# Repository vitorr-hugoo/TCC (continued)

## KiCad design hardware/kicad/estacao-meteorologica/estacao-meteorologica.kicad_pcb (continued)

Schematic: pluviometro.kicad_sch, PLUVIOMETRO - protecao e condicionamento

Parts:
C301, C302: 100 nF; C_0603_1608Metric; MPN CC0603KRX7R9BB104; LCSC C14663
D301: PESD5V0S1UL; D_SOD-882; MPN PESD5V0S1UL,315; LCSC C85402
D302: BAS70-04; SOT-23; MPN BAS70-04,215; LCSC C389351
J301: RJ11 6P6C, 90°; RJ11-TH_PCB-6P6C-90; MPN R-RJ11R06P-A800; LCSC C189750
R301: 10 kΩ; R_0603_1608Metric; MPN 0603WAF1002T5E; LCSC C25804
R302: 4.7 kΩ; R_0603_1608Metric; MPN 0603WAF4701T5E; LCSC C23162
R303: 1 kΩ; R_0603_1608Metric; MPN 0603WAF1001T5E; LCSC C21190
TP301: SENS_RAIN_RAW; TestPoint_Pad_D1.0mm; MPN N/A - elemento de cobre da PCB; LCSC N/A
TP302: SENS_RAIN_FILTERED; TestPoint_Pad_D1.0mm; MPN N/A - elemento de cobre da PCB; LCSC N/A
TP303: RAIN_PULSE; TestPoint_Pad_D1.0mm; MPN N/A - elemento de cobre da PCB; LCSC N/A
TP304: GND; TestPoint_Pad_D1.0mm; MPN N/A - elemento de cobre da PCB; LCSC N/A
U301: SN74LVC1G17DBVR; SOT-23-5; MPN SN74LVC1G17DBVR; LCSC C7836

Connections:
+3V3: C302.1, D302.2 (K), R303.1, U301.5 (VCC); also elsewhere on the board
/INTERFACES METEOROLÓGICAS/PLUVIÔMETRO/SENS_RAIN_RAW: D301.1 (K), J301.4, R301.2, R302.1, TP301.1
/INTERFACES METEOROLÓGICAS/RAIN_PULSE: TP303.1, U301.4; also elsewhere on the board
GND: C301.2, C302.2, D301.2 (A), D302.1 (A), R301.1, TP304.1, U301.3 (GND); also elsewhere on the board
unnamed: C301.1, D302.3 (COM), R302.2, TP302.1, U301.2
unnamed: J301.3, R303.2

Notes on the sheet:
ESD junto ao RJ11; clamp e C junto ao buffer. Plano GND continuo. Protecao transitoria a validar em bancada; sem isolamento e sem qualificacao contra raios.
R32=1k fornece +3V3 ao p3; R30=10k e o pull-down do p4. Reed aberto = 0 V; fechado = ~3,0 V e saida alta. C30=100n: tau de subida ~0,56 ms e de descida ~1,47 ms. PENDENCIA DE FIRMWARE: usar EXTI na subida e sem pull interno; o codigo atual ainda usa descida com pull-up.
3 SCHMITT / MCU
MISOL: contato reed passivo; cabo externo ~2 m; entrada individual 6P6C p3/p4.
2 FILTRO / CLAMP
1 CONECTOR / ESD

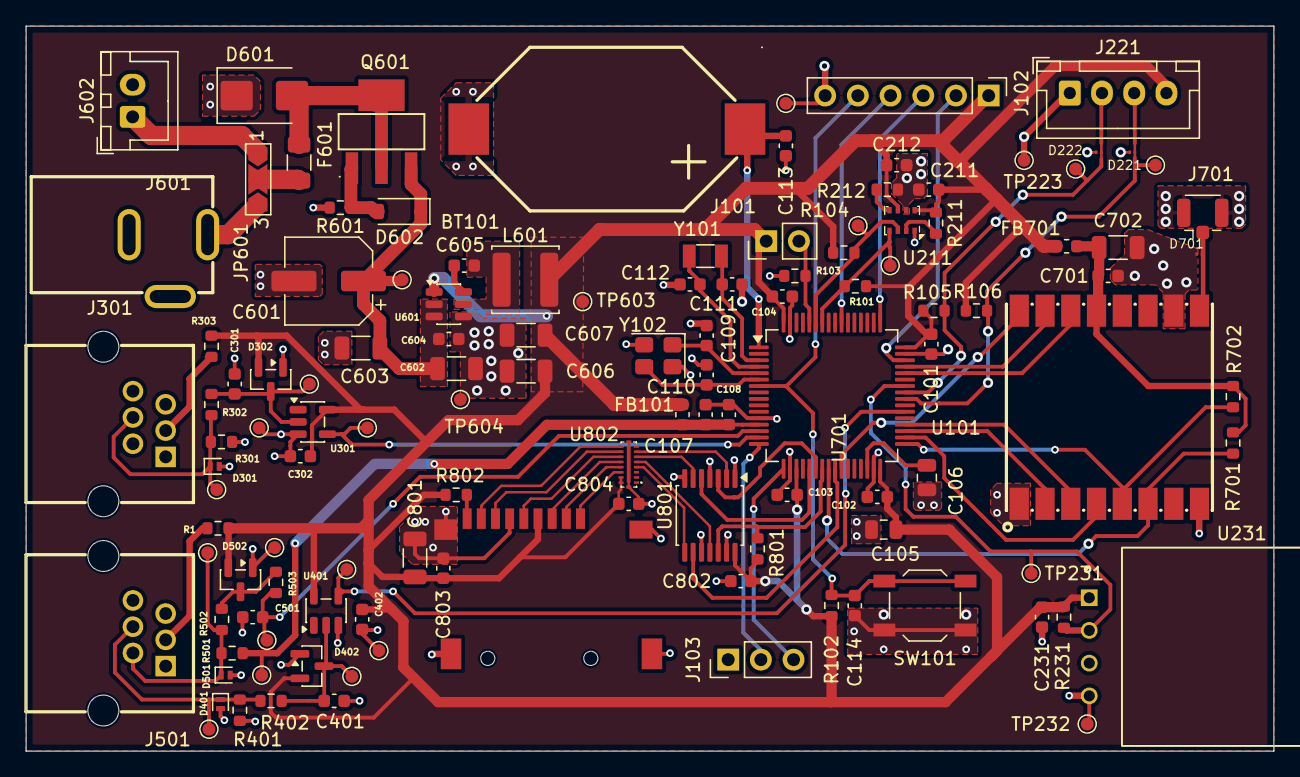
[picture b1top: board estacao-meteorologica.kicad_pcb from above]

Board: 2 copper layers, 96.9 x 56.3 mm, 125 parts (0 on the bottom side), 67 nets.

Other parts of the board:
C231: 100 nF; C_0603_1608Metric
R231: 10 kΩ; R_0603_1608Metric
TP231: DHT22_DATA; TestPoint_Pad_D1.0mm
TP232: GND; TestPoint_Pad_D1.0mm
U231: DHT22; DHT22_THT_P2.54mm_Vertical

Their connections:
+3V3: C231.1, R231.2, U231.1 (VDD); also elsewhere on the board
/MCU E DEPURAÇÃO/DHT22_DATA: R231.1, TP231.1, U231.2 (DATA); also elsewhere on the board
GND: C231.2, TP232.1, U231.4 (GND); also elsewhere on the board

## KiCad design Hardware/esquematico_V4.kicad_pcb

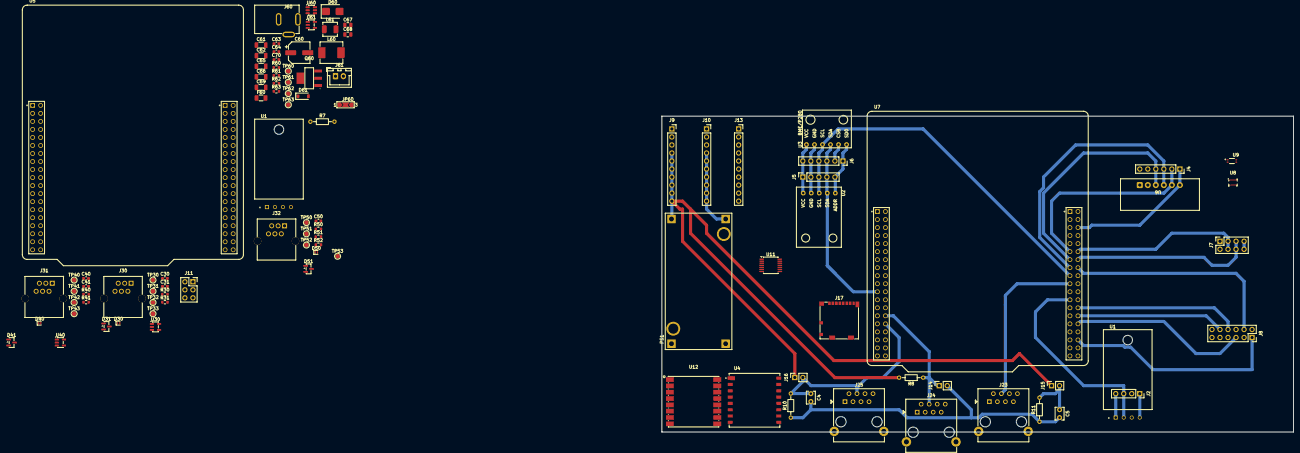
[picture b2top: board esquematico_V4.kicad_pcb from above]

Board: 2 copper layers, 200.0 x 100.0 mm, 101 parts (0 on the bottom side), 49 nets.

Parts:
C4, C5: 100n; C_Disc_D3.8mm_W2.6mm_P2.50mm
C30, C31, C41: 100n; C_0603_1608Metric
C40, C50: 10n; C_0603_1608Metric
C60: 47u / 35V; CP_Elec_6.3x5.8
C61, C62: 10u / 50V; C_1206_3216Metric
C63, C64: 100n / 50V; C_0603_1608Metric
C65, C66, C69: 22u / 25V; C_1206_3216Metric
C67, C68: 10u / 25V; C_0805_2012Metric
C70: 6p8 / 50V; C_0603_1608Metric
D30, D40, D50: PESD5V0S1UL; D_SOD-882
D31, D41, D51: BAS70-04; SOT-23
D60: SMBJ16CA; D_SMB
D61: BZT52C10 / 10V; D_SOD-123
F60: 1.5A / 32V lento; Fuse_1206_3216Metric
J2: Conn_DHT; PinSocket_1x04_P2.54mm_Vertical
J4: Conn_cartao_SD; PinSocket_1x06_P2.54mm_Vertical
J5: Conn_BH1750; PinSocket_1x05_P2.54mm_Vertical
J6: Conn_BMP; PinSocket_1x06_P2.54mm_Vertical
J7: Conn_Lora_4; PinSocket_2x04_P2.54mm_Vertical
J8: Conn_02x06_Row_Letter_Last; PinSocket_2x06_P2.54mm_Vertical
J9: Conn_+3v3; PinSocket_1x10_P2.54mm_Vertical
J10: Conn_GND; PinSocket_1x10_P2.54mm_Vertical
J11: Conn_01x02_Socket; PinSocket_2x03_P2.54mm_Vertical
J13: Conn_+5V; PinSocket_1x10_P2.54mm_Vertical
J14, J15, J16: Conn_01x02_Socket; PinSocket_1x02_P2.54mm_Vertical
J17: Micro_SD_Card; microSD_HC_Molex_104031-0811
J23, J24, J25: RJ45; RJ45_RCH_RC01937
J30, J31, J32: R-RJ11R06P-A800; RJ11-TH_PCB-6P6C-90
J60: P4 / DC-005-2.0; DC-IN-TH_DC-005-2.0_C22459640
J61: J_PWR / JST-XH; JST_XH_B2B-XH-A_1x02_P2.50mm_Vertical
JP60: SEL_FONTE; SolderJumper-3_P2.0mm_Open_TrianglePad1.0x1.5mm_NumberLabels
L60: 4u7 / MWSA0603S; L_Sunlord_MWSA0603S
L61: 2u2 / MWSA0402S; L_Sunlord_MWSA0402S
PS1: Lm2596; LM2596_modulo
Q60: DMP6023LE-13; SOT-223-4_L6.5-W3.5-P2.30-LS7.0-BR
R7, R8, R10, R11: 10k; R_Axial_DIN0204_L3.6mm_D1.6mm_P7.62mm_Horizontal
R30, R40, R50, R51: 10k; R_0603_1608Metric
R31, R41: 4k7; R_0603_1608Metric
R52: 1k; R_0603_1608Metric
R60, R63: 100k / 1%; R_0603_1608Metric
R61: 300k / 1%; R_0603_1608Metric
R62: 150k / 1%; R_0603_1608Metric
TP30: PLUVIOMETRO_RAW; TestPoint_Pad_D1.5mm
TP31: PLUVIOMETRO_FILT; TestPoint_Pad_D1.5mm
TP32: RAIN_PULSE; TestPoint_Pad_D1.5mm
TP33, TP43, TP53, TP63: GND; TestPoint_Pad_D1.5mm
TP40: ANEMOMETRO_RAW; TestPoint_Pad_D1.5mm
TP41: ANEMOMETRO_FILT; TestPoint_Pad_D1.5mm
TP42: WIND_SPEED_PULSE; TestPoint_Pad_D1.5mm
TP50: WIND_DIR_RAW; TestPoint_Pad_D1.5mm
TP51: WIND_DIR_ADC; TestPoint_Pad_D1.5mm
TP52: VREF_SENSOR; TestPoint_Pad_D1.5mm
TP60: VIN_MAIN; TestPoint_Pad_D1.5mm
TP61: +5V; TestPoint_Pad_D1.5mm
TP62: +3V3; TestPoint_Pad_D1.5mm
U1, U1#2: DHT22; XDCR_DHT22
U2: module_bh1750; bh1750_modulo
U3: module_bme280; bme280_modulo
U4: Lora_Sx1276; SX1276_modulo
U5, U7: NUCLEO-F446RE; MODULE_NUCLEO-F446RE
U6: MicroSD Card Adapter; Micro_SD_Card_Adapter
U8: BMP280; Bosch_LGA-8_2x2.5mm_P0.65mm_ClockwisePinNumbering
U9: BH1750FVI-TR; BH1750FVI-TR_sensor
U11: 74LVC125; TSSOP-14_4.4x5mm_P0.65mm
U12: LORA1276-C1-915MHZ; COMM-SMD_LORA1276-C1-915MHZ
U30, U40: SN74LVC1G17DBVR; SOT-23-5
U60: AP63205WU-7; TSOT-23-6
U61: TLV62569DBVR; SOT-23-5

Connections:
+3V3: C31.1, C41.1, C68.1, C69.1, C70.1, D31.2 (K), D41.2 (K), D51.2 (K), J5.1, J6.2, J6.6, J7.7, J7.8, J9.1, J9.2, J9.3, J9.4, J9.5, J9.6, J9.7, J9.8, J9.9, J9.10, J15.1, J16.1, J17.4 (VDD), L61.2, PS1.OUT+, R8.2, R30.1, R40.1, R61.1, TP62.1, U2.5 (VCC), U3.1 (VCC), U3.5 (CSB), U4.3 (3.3V), U8.6 (VDDIO), U9.1 (VCC), U11.7 (GND), U12.13 (VCC), U30.5 (VCC), U40.5 (VCC)
+5V: C65.1, C66.1, C67.1, J4.5, L60.2, R7.2, TP61.1, U1#2.1 (VDD), U5.CN7_18 (CN7_+5V), U6.2 (VCC), U11.14 (VCC), U60.1 (FB), U61.1 (EN), U61.4 (VIN)
/DHT22/PA8: R7.1, U1#2.2 (DATA)
/METEOROLOGIA/ANEMOMETRO/ANEMOMETRO_RAW: D40.1 (K), J31.4, R40.2, R41.1, TP40.1
/METEOROLOGIA/BIRUTA/WIND_DIR_RAW: D50.1 (K), J32.4, R50.2, R51.1, TP50.1
/METEOROLOGIA/PLUVIOMETRO/PLUVIOMETRO_RAW: D30.1 (K), J30.4, R30.2, R31.1, TP30.1
/alimentacao/ENERGIA_POS: J61.1, JP60.1 (A)
/alimentacao/FB_3V3: C70.2, R62.2, R63.1, U61.5 (FB)
/alimentacao/P4_POS: J60.1, JP60.3 (B)
/alimentacao/VIN_MAIN: C60.1, C61.1, C62.1, C63.1, D61.1 (K), Q60.3 (S), TP60.1, U60.2 (EN), U60.3 (IN)
ANT_EXT: U4.1 (ANT), U12.9 (ANT)
CS_LLS: J17.2 (DAT3/CD), U11.11
DI_LLS: J17.3 (CMD), U11.3
DO_LLS: J17.7 (DAT0), U11.5
GND: C30.2, C31.2, C40.2, C41.2, C50.2, C60.2, C61.2, C62.2, C63.2, C65.2, C66.2, C67.2, C68.2, C69.2, D30.2 (A), D31.1 (A), D40.2 (A), D41.1 (A), D50.2 (A), D51.1 (A), D60.1 (A1), J4.6, J5.2, J5.5, J6.1, J6.5, J17.6 (VSS), J17.10 (DET_A), J17.11 (SHIELD), J30.3, J31.3, J32.3, J60.2, J61.2, R60.2, R63.2, TP33.1, TP43.1, TP53.1, TP63.1, U1#2.4 (GND), U2.1 (ADDR), U2.4 (GND), U3.2 (GND), U3.6 (SDO), U5.CN7_8 (CN7_GND), U5.CN7_19 (CN7_GND), U5.CN7_20 (CN7_GND), U5.CN7_22 (CN7_GND), U5.CN10_9 (CN10_GND), U5.CN10_20 (CN10_GND), U5.CN10_32 (AGND), U6.1 (GND), U8.1 (GND), U8.7 (GND), U9.3 (GND), U11.1, U11.4, U11.10, U11.13, U12.1 (GND), U12.8 (GND), U12.10 (GND), U30.3 (GND), U40.3 (GND), U60.4 (GND), U61.2 (GND)
Gnd: C4.2, C5.2, J2.1, J8.11, J8.12, J10.1, J10.2, J10.3, J10.4, J10.5, J10.6, J10.7, J10.8, J10.9, J10.10, J14.2, PS1.IN-, PS1.OUT-, R10.1, R11.1, U1.4 (GND), U4.2 (GND), U4.9 (GND), U4.16 (GND), U7.CN7_8 (CN7_GND), U7.CN7_19 (CN7_GND), U7.CN7_20 (CN7_GND), U7.CN7_22 (CN7_GND), U7.CN10_9 (CN10_GND), U7.CN10_20 (CN10_GND)
unnamed: C30.1, D31.3 (COM), R31.2, TP31.1, U30.2
unnamed: C40.1, D41.3 (COM), R41.2, TP41.1, U40.2
unnamed: D51.3 (COM), R51.2, R52.1
unnamed: D60.2 (A2), F60.2, Q60.2 (D), Q60.4 (D)
unnamed: D61.2 (A), Q60.1 (G), R60.1
unnamed: F60.1, JP60.2 (C)
unnamed: R61.2, R62.1
unnamed: C64.1, U60.6 (BST)
unnamed: C64.2, L60.1, U60.5 (SW)
unnamed: L61.1, U61.3 (SW)
PA0: J14.1, J24.4, R8.1, U7.CN7_28 (PA0)
PA1: C4.1, J16.2, J25.4, R10.2, U7.CN7_30 (PA1)
PA5: J4.2, U5.CN10_11 (PA5), U6.5 (SCK), U7.CN10_11 (PA5)
PA6: J4.4, U5.CN10_13 (PA6), U6.3 (MISO), U7.CN10_13 (PA6)
PA7: J4.3, U5.CN10_15 (PA7), U6.4 (MOSI), U7.CN10_15 (PA7)
PA8: J2.3, U1.2 (DATA), U5.CN10_23 (PA8), U7.CN10_23 (PA8)
PA11: J7.5, J7.6, U4.5 (DIO0), U5.CN10_14 (PA11), U7.CN10_14 (PA11)
PA12: J7.3, J7.4, U4.6 (DIO1), U5.CN10_12 (PA12), U7.CN10_12 (PA12)
PB6: J5.3, J6.4, J11.1, J11.2, J11.3, U2.3 (SCL), U3.3 (SCL)
PB7: J5.4, J6.3, J11.4, J11.5, J11.6, U2.2 (SDA), U3.4 (SDA)
PB12: J8.3, J8.4, U4.15 (NSS), U5.CN10_16 (PB12), U7.CN10_16 (PB12)
PB13: J8.5, J8.6, U4.12 (SCK), U5.CN10_30 (PB13), U7.CN10_30 (PB13)
PB14: J8.9, J8.10, U4.13 (MISO), U5.CN10_28 (PB14), U7.CN10_28 (PB14)
PB15: J8.7, J8.8, U4.14 (MOSI), U5.CN10_26 (PB15), U7.CN10_26 (PB15)
PC4: J8.1, J8.2, U4.4 (RESET), U5.CN10_34 (PC4), U7.CN10_34 (PC4)
PC5: J4.1, U5.CN10_6 (PC5), U6.6 (CS), U7.CN10_6 (PC5)
PC7: C5.1, J15.2, J23.4, R11.2, U7.CN10_19 (PC7)
RAIN_PULSE: TP32.1, U5.CN7_30 (PA1), U30.4
SCK_LLS: J17.5 (CLK), U11.8
VCC: J2.4, J13.1, J13.2, J13.3, J13.4, J13.5, J13.6, J13.7, J13.8, J13.9, J13.10, U1.1 (VDD), U7.CN7_18 (CN7_+5V)
VREF_SENSOR: R50.1, TP52.1, U5.CN10_7 (AVDD)
WIND_DIR_ADC: C50.1, R52.2, TP51.1, U5.CN7_28 (PA0)
WIND_SPEED_PULSE: TP42.1, U5.CN10_19 (PC7), U40.4

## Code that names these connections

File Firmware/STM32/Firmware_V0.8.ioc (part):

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Mcu.Name=STM32F446R(C-E)Tx
Mcu.Package=LQFP64
Mcu.UserName=STM32F446RETx
PA0-WKUP.Signal=ADCx_IN0
PA1.GPIOParameters=GPIO_PuPd,GPIO_Label,GPIO_ModeDefaultEXTI
PA1.GPIO_Label=PLUV_RAIN
PA1.GPIO_ModeDefaultEXTI=GPIO_MODE_IT_FALLING
PA1.GPIO_PuPd=GPIO_PULLUP
PA1.Signal=GPXTI1
PA11.GPIOParameters=GPIO_Label
PA11.GPIO_Label=LORA_DIO0
PA11.Signal=GPXTI11
PA12.GPIOParameters=GPIO_Label
PA12.GPIO_Label=LORA_DIO1
PA12.Signal=GPXTI12
PA13.GPIOParameters=GPIO_Label
PA13.GPIO_Label=TMS
PA13.Mode=Serial_Wire
PA13.Signal=SYS_JTMS-SWDIO
PA14.GPIOParameters=GPIO_Label
PA14.GPIO_Label=TCK
PA14.Mode=Serial_Wire
PA14.Signal=SYS_JTCK-SWCLK
PA2.GPIOParameters=GPIO_Label
PA2.GPIO_Label=USART_TX
PA2.Mode=Asynchronous
PA2.Signal=USART2_TX
PA3.GPIOParameters=GPIO_Label
PA3.GPIO_Label=USART_RX
PA3.Mode=Asynchronous
PA3.Signal=USART2_RX
PA5.Mode=Full_Duplex_Master
PA5.Signal=SPI1_SCK
PA6.Mode=Full_Duplex_Master
PA6.Signal=SPI1_MISO
PA7.Mode=Full_Duplex_Master
PA7.Signal=SPI1_MOSI
PA8.GPIOParameters=GPIO_Speed,PinState,GPIO_Label
PA8.GPIO_Label=DHT22
PA8.GPIO_Speed=GPIO_SPEED_FREQ_HIGH
PA8.PinState=GPIO_PIN_SET
PA8.Signal=GPIO_Output
PB0.GPIOParameters=GPIO_Speed,PinState,GPIO_Label
PB0.GPIO_Label=LORA_NSS
PB0.GPIO_Speed=GPIO_SPEED_FREQ_VERY_HIGH
PB0.PinState=GPIO_PIN_SET
PB0.Signal=GPIO_Output
PB13.Mode=Full_Duplex_Master
PB13.Signal=SPI2_SCK
PB14.Mode=Full_Duplex_Master
PB14.Signal=SPI2_MISO
PB15.Mode=Full_Duplex_Master
PB15.Signal=SPI2_MOSI
PB3.GPIOParameters=GPIO_Label
PB3.GPIO_Label=SWO
PB3.Signal=SYS_JTDO-SWO
PB6.Mode=I2C
PB6.Signal=I2C1_SCL
PB7.Mode=I2C
PB7.Signal=I2C1_SDA
PC14-OSC32_IN.Mode=LSE-External-Oscillator
PC14-OSC32_IN.Signal=RCC_OSC32_IN
PC15-OSC32_OUT.Mode=LSE-External-Oscillator
PC15-OSC32_OUT.Signal=RCC_OSC32_OUT
PC4.GPIOParameters=PinState,GPIO_Label
PC4.GPIO_Label=LORA_RST
PC4.PinState=GPIO_PIN_SET
PC4.Signal=GPIO_Output
PC5.GPIOParameters=PinState,GPIO_Label
PC5.GPIO_Label=SD_CS
PC5.PinState=GPIO_PIN_SET
PC5.Signal=GPIO_Output
PC7.GPIOParameters=GPIO_PuPd,GPIO_Label,GPIO_ModeDefaultEXTI
PC7.GPIO_Label=ANEM_SPEED
PC7.GPIO_ModeDefaultEXTI=GPIO_MODE_IT_FALLING
PC7.GPIO_PuPd=GPIO_PULLUP
PC7.Signal=GPXTI7
PH0-OSC_IN.Mode=HSE-External-Oscillator
PH0-OSC_IN.Signal=RCC_OSC_IN
PH1-OSC_OUT.Mode=HSE-External-Oscillator
PH1-OSC_OUT.Signal=RCC_OSC_OUT
RCC.HSE_VALUE=8000000
RCC.SYSCLKFreq_VALUE=180000000
RCC.SYSCLKSource=RCC_SYSCLKSOURCE_PLLCLK
board=NUCLEO-F446RE
boardIOC=true

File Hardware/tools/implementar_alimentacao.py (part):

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s.wire(j['1'],(63.5,93.98),(63.5,80.01),(85.09,80.01),(85.09,74.93))
s.wire(j['2'],(43.18,91.44),(43.18,99.06));s.gnd((43.18,99.06))
jp=s.sym('JP','JP60',(85.09,69.85),90,field=(92.71,48.26),role='1-2 = J61; 2-3 = J60; aberto de fabrica, fechar na configuracao')
s.label('P4_POS',(55.88,54.61));s.label('ENERGIA_POS',(64.77,80.01))
f=s.sym('F','F60',(111.76,69.85),90,field=(102.87,57.15),role='Protecao local; fonte externa limitada a <=2A; VRLA requer fusivel junto a bateria')
s.wire(jp['2'],f['1'])
d=s.sym('TVS','D60',(137.16,92.71),90,field=(143.51,90.17),role='TVS bidirecional depois do fusivel e antes do PMOS; surtos limitados')
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s.shunt('10u','C61',279.4,92.71,69.85,113.03,'MLCC de entrada do AP63205; junto ao VIN/GND')
s.shunt('10u','C62',304.8,92.71,69.85,113.03,'Reserva de capacitancia efetiva sob bias 16V')
s.shunt('100n','C63',330.2,92.71,69.85,113.03,'Desacoplamento HF junto ao CI')
s.label('VIN_MAIN',(355.6,69.85));s.sym('TP','TP60',(355.6,59.69),value='VIN_MAIN',field=(350.52,50.8));s.wire((355.6,59.69),(355.6,69.85));s.dot((355.6,69.85))
s.sym('FLAG','#FLG060',(370.84,69.85));s.sym('FLAG','#FLG061',(370.84,113.03));s.gnd((370.84,113.03))
s.text('JP60 aberto: placa desligada. Fechar SOMENTE 1-2 (J_PWR) ou 2-3 (P4).\nNunca fechar os tres pads. Desenergizar antes de alterar. GNDs sao comuns.',(20.32,118.11),1.27)
s.text('Nao conectar bateria sem LVD/fusivel externo. Nao ha OR automatico nesta PCB.\nTVS nao protege contra sobretensao sustentada nem raio direto.',(254,120.65),1.27)

# 5 V buck and explicit feedback loop. Upper SW route, bootstrap underneath.
u=s.sym('BUCK5','U60',(76.2,175.26),field=(63.5,155.0),role='Converte VIN_MAIN para5V; EN ligado aVIN; FB direto na saida filtrada')
s.label('VIN_MAIN',(27.94,172.72));s.wire((27.94,172.72),(55.88,172.72),u['3']);s.wire((55.88,172.72),(55.88,177.8),u['2']);s.dot((55.88,172.72))
l=s.sym('L5','L60',(124.46,172.72),90,field=(111.76,160.02),role='Armazena energia e filtra SW; blindado; nao e bead')
s.wire(u['5'],(93.98,172.72),l['1']);s.wire(l['2'],(154.94,172.72),(180.34,172.72),(200.66,172.72))
c=s.sym('100n','C64',(101.6,191.77),90,field=(92.71,198.12),role='Bootstrap entre BST6 e SW5; nunca aGND')
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s.wire((302.26,213.36),r['1']);s.wire(r['2'],(302.26,238.76));s.gnd((302.26,238.76))
c=s.sym('6p8','C70',(325.12,196.85),role='Feed-forward em paralelo comR61+R62; resposta de transientes')
s.wire((325.12,172.72),c['1']);s.wire(c['2'],(325.12,213.36),(302.26,213.36));s.dot((325.12,172.72));s.dot((302.26,213.36))
s.wire(u['5'],(269.24,175.26),(269.24,213.36),(302.26,213.36));s.label('FB_3V3',(276.86,213.36))
s.wire(u['2'],(256.54,207.01));s.gnd((256.54,207.01))
s.sym('TP','TP62',(388.62,160.02),value='+3V3',field=(383.54,149.86));s.wire((388.62,160.02),(388.62,172.72));s.dot((388.62,172.72))
s.sym('FLAG','#FLG063',(391.16,172.72));s.label('+3V3',(391.16,172.72),'hierarchical_label',180,'output')
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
